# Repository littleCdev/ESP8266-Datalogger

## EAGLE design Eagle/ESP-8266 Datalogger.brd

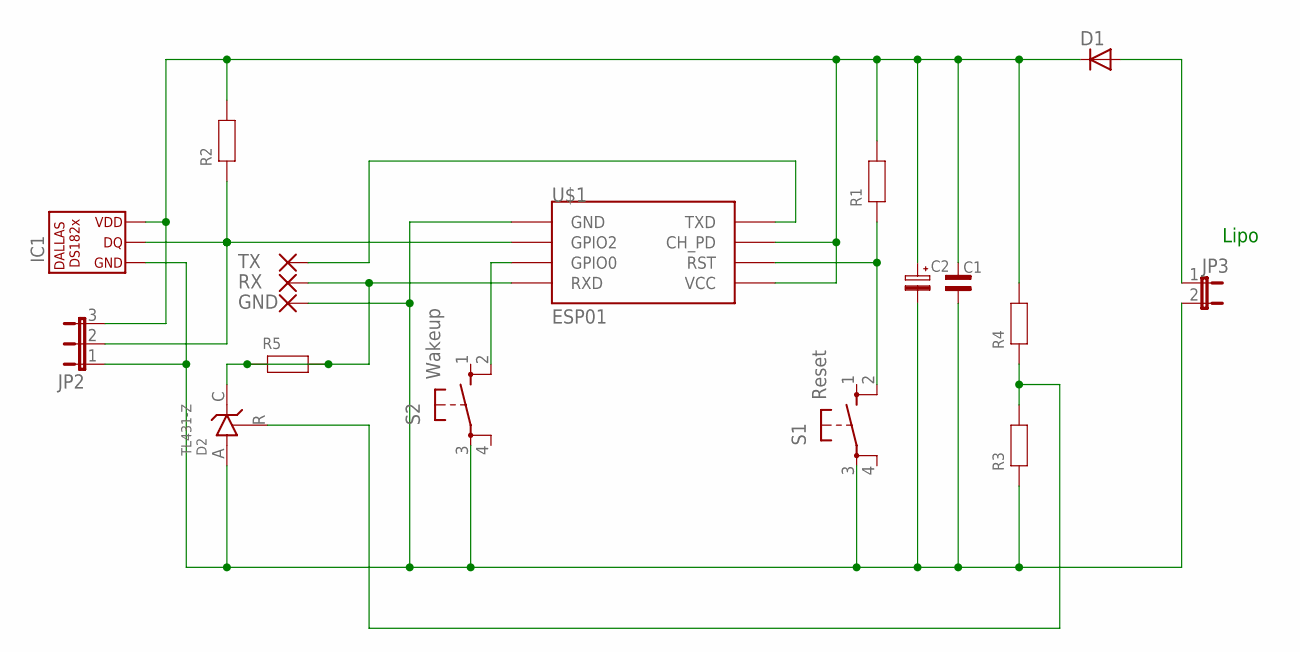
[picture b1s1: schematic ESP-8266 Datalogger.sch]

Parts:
C1: C-C1206; C1206
C2: ELKO-SMC_B; SMC_B
D1: BYS10; SOD106A
D2: TL431-Z; TO92-Z
GND: 1,6/0,8
IC1: DS182X-L; TO92-
JP2: JP2E; JP2
JP3: JP1E; JP1
R1, R2, R3, R4: R-R1206; R1206
R5: R400MIL; RES400
RX: 1,6/0,8
S1: Reset; B3F-10XX
S2: Wakeup; B3F-10XX
TX: 1,6/0,8
U$1: ESP01

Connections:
GND: C1.2, C2.- (2), D2.A, GND.1, IC1.C (1), JP2.1, JP3.2, R3.1, S1.3, S2.3, U$1.GND
unnamed: D1.A, JP3.1
unnamed: D2.R, R3.2, R4.1
unnamed: D2.C, R5.1, R5.2, RX.1, U$1.RX (RXD)
unnamed: TX.1, U$1.TX (TXD)
unnamed: S2.2, U$1.GPIO0
unnamed: R1.1, S1.2, U$1.RST
unnamed: IC1.B (2), JP2.2, R2.1, U$1.GPIO2
VCC: C1.1, C2.+ (1), D1.K, IC1.E (3), JP2.3, R1.2, R2.2, R4.2, U$1.CH_PD, U$1.VCC

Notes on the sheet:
Lipo

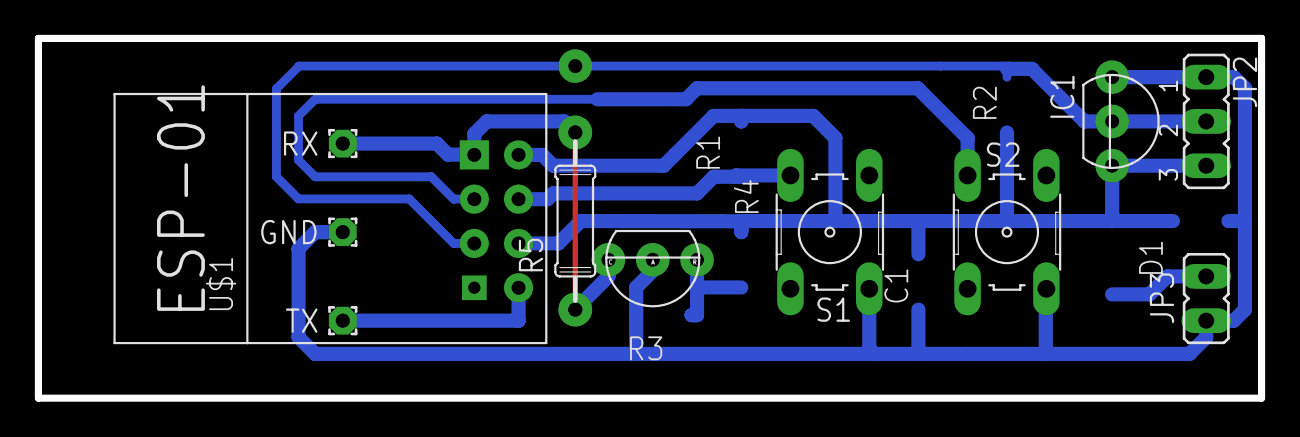
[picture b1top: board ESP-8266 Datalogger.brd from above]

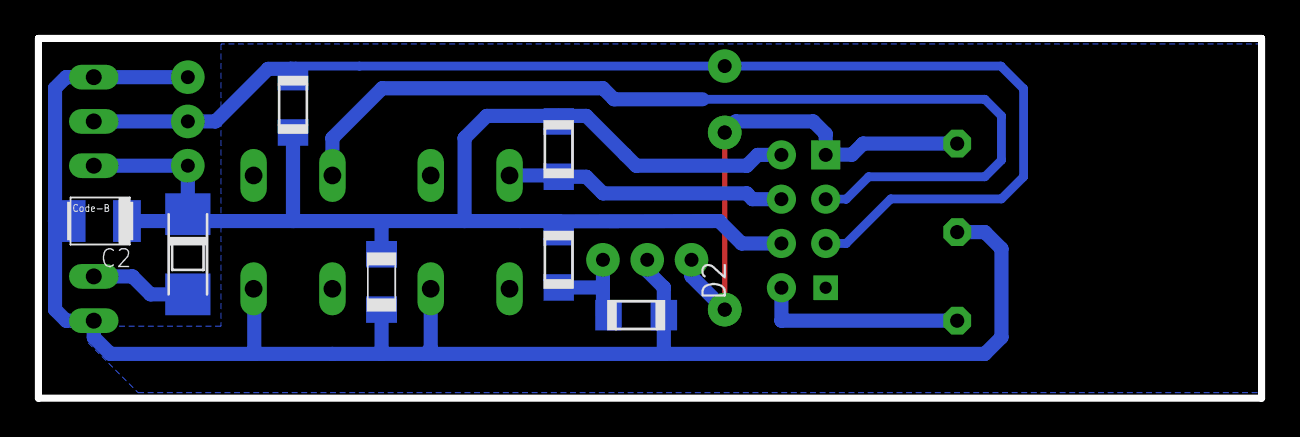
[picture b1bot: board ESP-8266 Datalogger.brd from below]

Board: 4 copper layers, 70.2 x 20.6 mm, 18 parts (7 on the bottom side), 9 nets.
